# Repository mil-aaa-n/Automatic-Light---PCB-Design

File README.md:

# Automatic-Light---PCB-Design
(EXPERIMENTAL) an automatic street light circuit designed on a PCB using LDR and BJT with the help of KiCad software. Simulated on Proteus first.

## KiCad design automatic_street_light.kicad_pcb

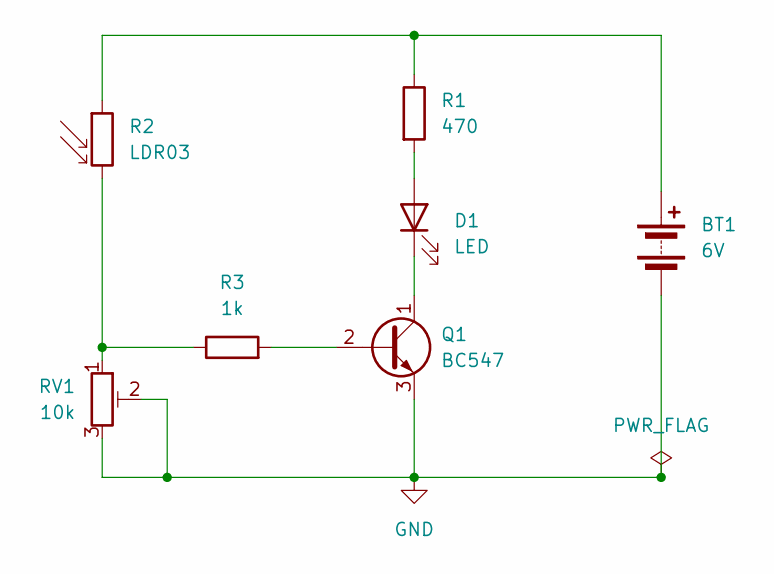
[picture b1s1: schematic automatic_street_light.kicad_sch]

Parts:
BT1: 6V; PinHeader_1x02_P2.54mm_Horizontal
D1: LED; LED_D5.0mm
Q1: BC547; TO-92_Inline
R1: 470; R_Axial_DIN0207_L6.3mm_D2.5mm_P7.62mm_Horizontal
R2: LDR03; R_LDR_10x8.5mm_P7.6mm_Vertical
R3: 1k; R_Axial_DIN0207_L6.3mm_D2.5mm_P7.62mm_Horizontal
RV1: 10k; Potentiometer_Alps_RK163_Single_Horizontal

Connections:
GND: BT1.2 (-), Q1.3 (E), RV1.2, RV1.3
unnamed: BT1.1 (+), R1.1, R2.1
unnamed: D1.2 (A), R1.2
unnamed: D1.1 (K), Q1.1 (C)
unnamed: Q1.2 (B), R3.2
unnamed: R2.2, R3.1, RV1.1

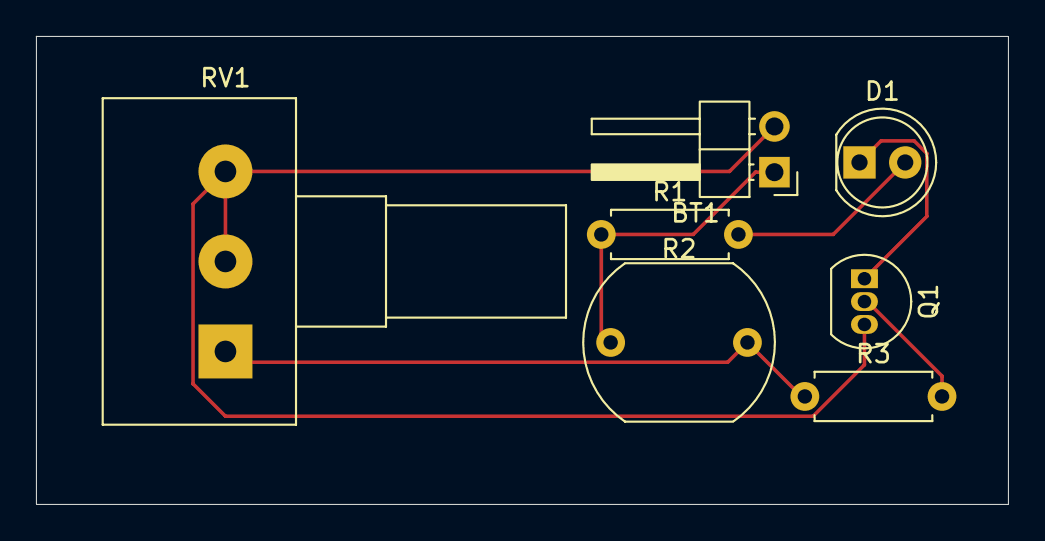
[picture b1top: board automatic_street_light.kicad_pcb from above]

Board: 2 copper layers, 54.0 x 26.0 mm, 7 parts (0 on the bottom side), 6 nets.
